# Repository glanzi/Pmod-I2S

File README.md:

# Pmod I2S - Stereo Audio Output 

The Pmod I2S board is a stereo audio output based on a CS4344 Stereo D/A converter from Cirrus Logic.
This board is based on and compatible with Eric Brombaugh's [I2S Audio DAC](http://ebrombaugh.studionebula.com/synth/audiodac/index.html) project.

## License
The Pmod I2S project is an open source project licensed under CERN Open Hardware Licence v1.2. Please see the included LICENSE file for details. If you do wish to distribute boards derived from this open source hardware project then you must also release the source files for the boards under CERN Open Hardware Licence v1.2. You are free to do this, but please improve upon the original design and provide a tangible benefit for users of the board.

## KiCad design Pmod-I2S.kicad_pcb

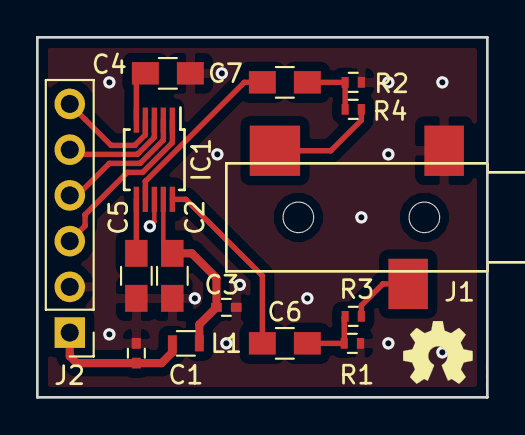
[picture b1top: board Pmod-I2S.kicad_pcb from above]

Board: 2 copper layers, 25.0 x 20.0 mm, 15 parts (0 on the bottom side), 15 nets.

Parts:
C1, C3: 0.1uF; C_0402
C2: 1uF; C_0805_HandSoldering
C4, C6, C7: 3.3uF; C_0805_HandSoldering
C5: 10uF; C_0805_HandSoldering
IC1: CS4344; MSOP-10_3x3mm_Pitch0.5mm
J1: SJ-3523-SMT
J2: 1x06; Pin_Header_Straight_1x06_Pitch2.54mm
L1: 2.5K; L_0603
R1, R2: 10K; R_0402
R3, R4: 470; R_0402

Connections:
/LRCK: IC1.3, J2.5
/MCLK: IC1.4, J2.6
/SCLK: IC1.2, J2.4
/SDIN: IC1.1, J2.3
/VCC: C1.1, J2.1, L1.1
GND: C1.2, C2.2, C3.2, C4.2, C5.2, IC1.8, J1.1, J2.2, R1.2, R2.2
unnamed: C2.1, C3.1, IC1.9, L1.2
unnamed: C4.1, IC1.5
unnamed: C5.1, IC1.6
unnamed: C6.1, R1.1, R3.2
unnamed: C6.2, IC1.10
unnamed: C7.1, R2.1, R4.2
unnamed: C7.2, IC1.7
unnamed: J1.2, R4.1
unnamed: J1.3, R3.1

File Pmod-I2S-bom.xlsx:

Qty | Ref | MPN | Desc | Digi-Key | Mouser
1 | IC1 | CS4344-CZZ | IC DAC 24BIT 192KHZ 10-TSSOP | 598-1051-5-ND
1 | J1 | SJ-3523-SMT-TR | CONN JACK STEREO 3.5MM SMD R/A | CP-3523SJCT-ND
1 | J2 |  | CONN HEADER 6 POS 2.54
1 | L1 | BLM18BD252SN1D | FERRITE BEAD 2.5 KOHM 0603 1LN | 490-1028-1-ND
3 | C1, C2, C3 |  | 0.1uF Ceramic Capacitor, 16V, X7R, 10%, 0402
3 | C4, C6, C7 |  | 3.3uF Ceramic Capacitor, 16V, X7R, 10%, 0402
1 | C5 |  | 10uF Ceramic Capacitor, 16V, X7R, 10%, 0402
2 | R1, R2 |  | 10k resistor, 1% tolerance, 1/16 watt, 0402
2 | R3, R4 |  | 470ohm resistor, 1% tolerance, 1/16 watt, 0402

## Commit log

2018-11-18 Add comments
2018-11-18 Update comments
2018-11-18 Add BOM
